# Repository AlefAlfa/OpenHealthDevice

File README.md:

# Open Health Device

The **Open Health Device** is an open-source, low-power wearable designed for continuous health monitoring. Built around the Nordic nRF52840 microcontroller and featuring BLE (Bluetooth Low Energy) support, it offers a customizable and privacy-focused alternative to proprietary fitness trackers.

## Features

* 24/7 health data collection
* BLE communication with iOS and other platforms
* Built for power efficiency and long battery life
* Modular sensor architecture
* Fully open-source firmware and hardware design

## Use Cases

* Personalized wellness tracking
* Sleep and activity monitoring
* Open research and prototyping
* Biohacking and quantified self

## Who It's For

This device is ideal for:

* Developers
* Researchers
* Hardware hackers
* Health tech enthusiasts

## Status

Currently in hardware prototyping and firmware development. Contributions welcome!

## License

MIT License

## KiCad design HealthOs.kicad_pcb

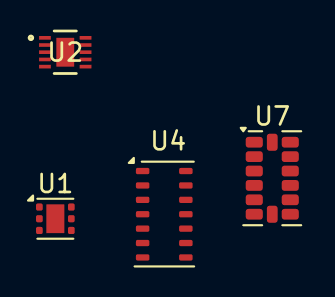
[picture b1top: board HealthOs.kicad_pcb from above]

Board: 2 copper layers, 4 parts (0 on the bottom side), 6 nets, no tracks yet.

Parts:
U1: TLV75533PDRV; WSON-6-1EP_2x2mm_P0.65mm_EP1x1.6mm
U2: PQ25186DLHR; WSON10_DLH_TEX
U4: MAX30102; Maxim_OLGA-14_3.3x5.6mm_P0.8mm
U7: ADXL343; LGA-14_3x5mm_P0.8mm_LayoutBorder1x6y

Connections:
+3V3: U4.9 (VLED+), U4.10 (VLED+), U7.1 (Vdd_I/O), U7.3 (RES), U7.6 (Vs), U7.7 (~CS)
-BATT: U1.3 (GND), U1.7 (GND), U2.5 (GND)
Earth: U4.12 (GND), U7.2 (GND), U7.4 (GND), U7.5 (GND), U7.11 (RES), U7.12 (SDO/ADDR)
unnamed: U1.6 (IN), U2.1 (SYS)
unnamed: U4.2 (SCL), U7.14 (SCL/SCLK)
unnamed: U4.3 (SDA), U7.13 (SDA/SDI/SDIO)

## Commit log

2025-05-11 Import KiCad project files
2025-05-11 Remove tracked KiCad autosaves, backups & caches
2025-05-11 Ignore KiCad backups, autosaves & lock files
2025-05-11 Don’t ignore .kicad_prl; we need that in repo
2025-05-11 Import KiCad project files (including .kicad_prl)
